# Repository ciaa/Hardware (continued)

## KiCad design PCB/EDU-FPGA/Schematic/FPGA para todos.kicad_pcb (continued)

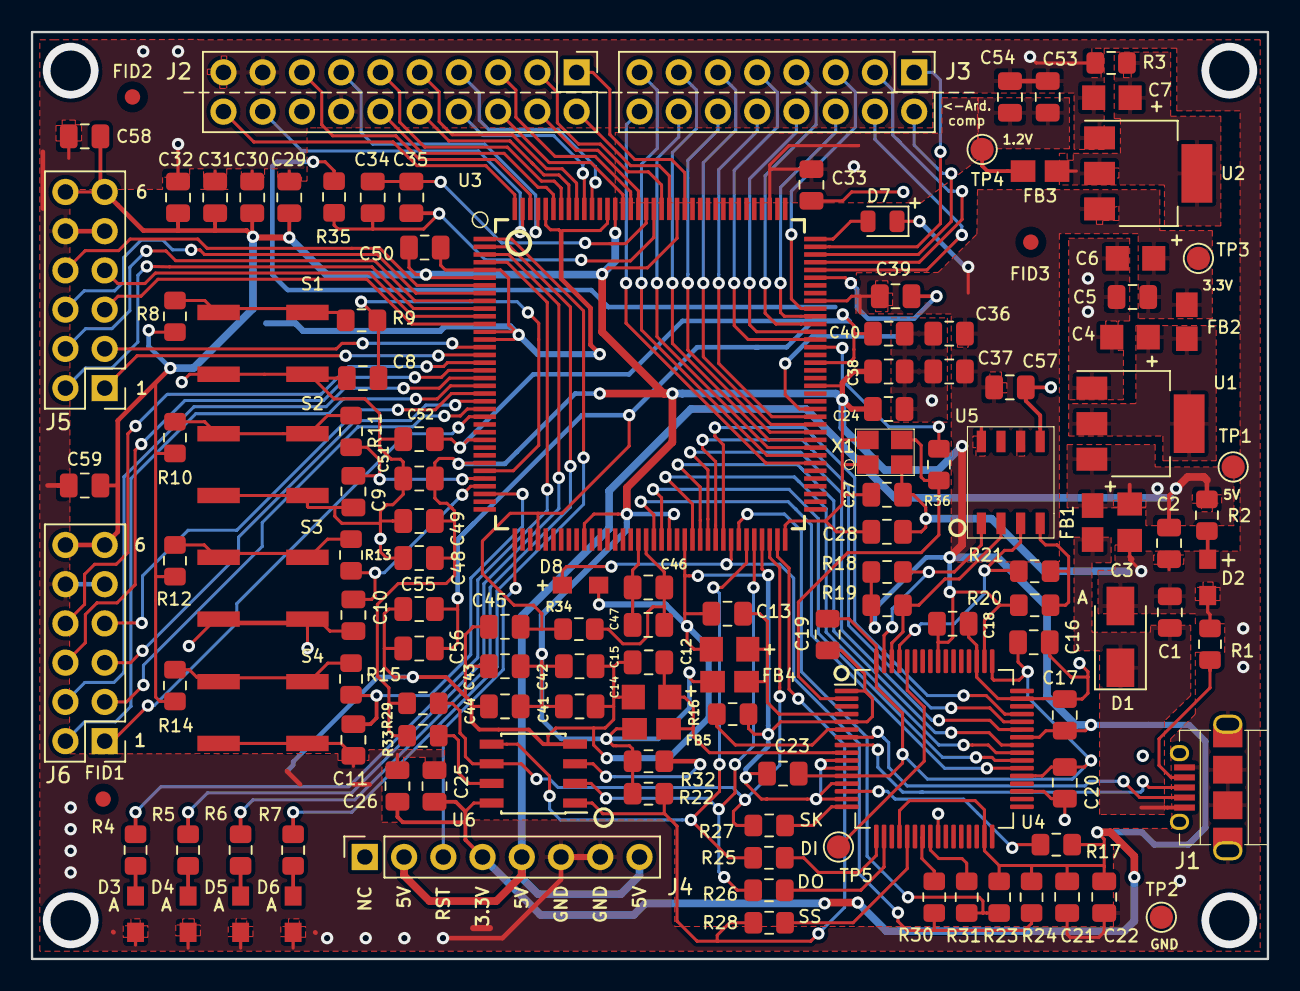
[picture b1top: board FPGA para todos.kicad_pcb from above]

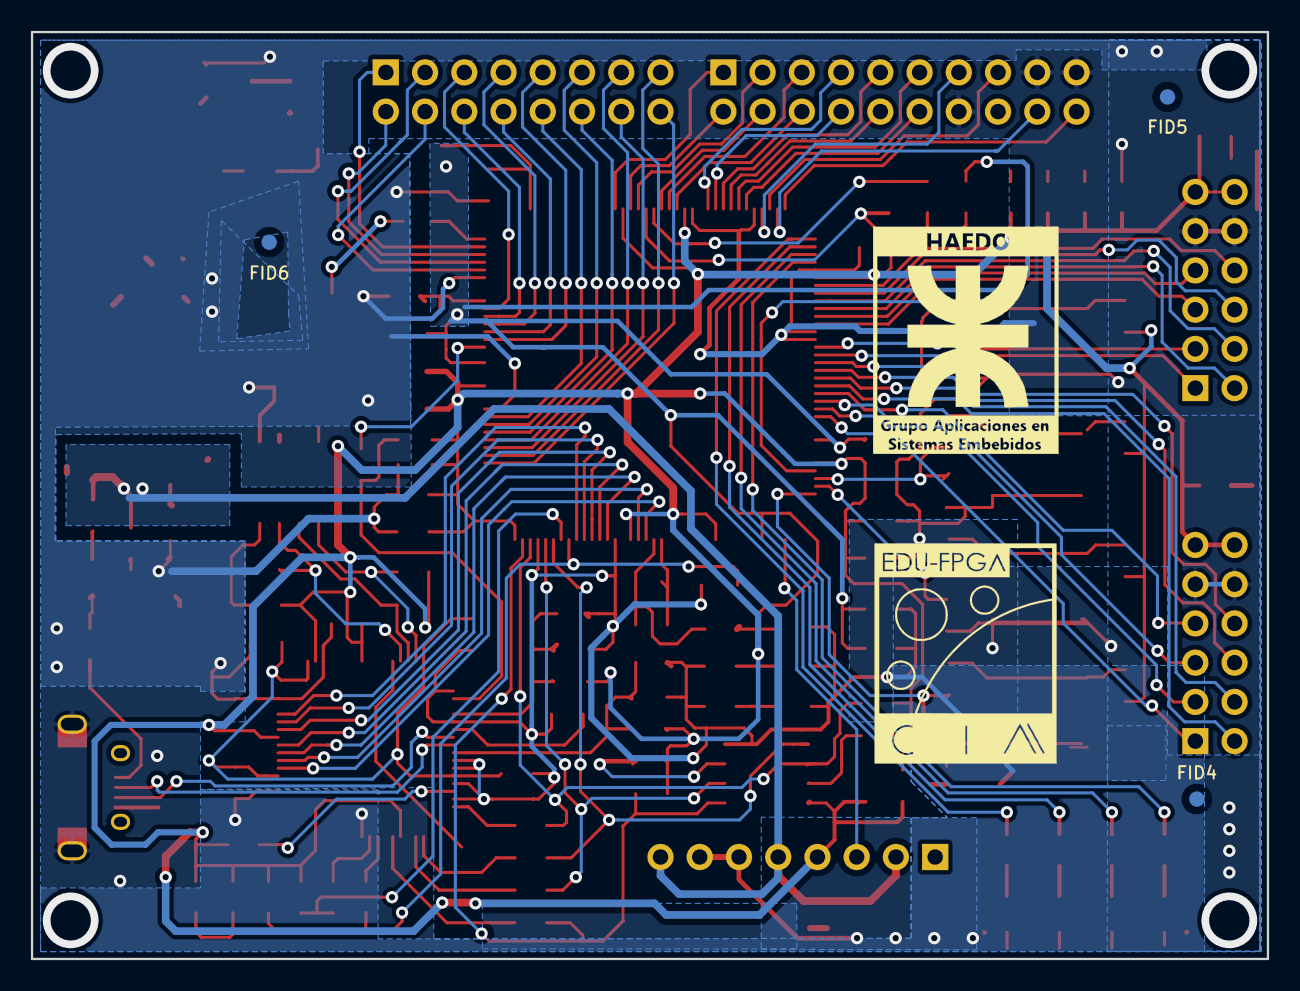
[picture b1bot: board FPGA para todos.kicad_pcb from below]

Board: 2 copper layers, 80.0 x 60.0 mm, 136 parts (3 on the bottom side), 114 nets.

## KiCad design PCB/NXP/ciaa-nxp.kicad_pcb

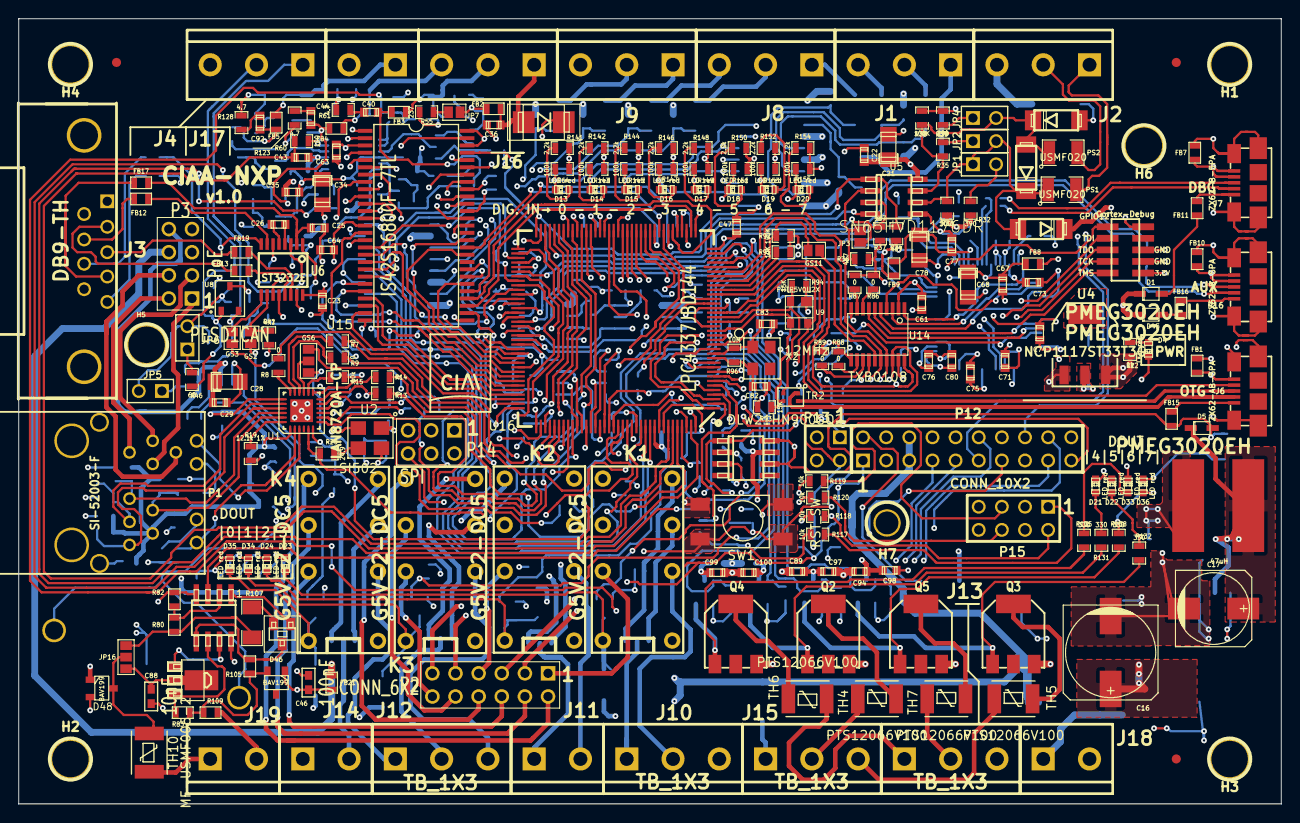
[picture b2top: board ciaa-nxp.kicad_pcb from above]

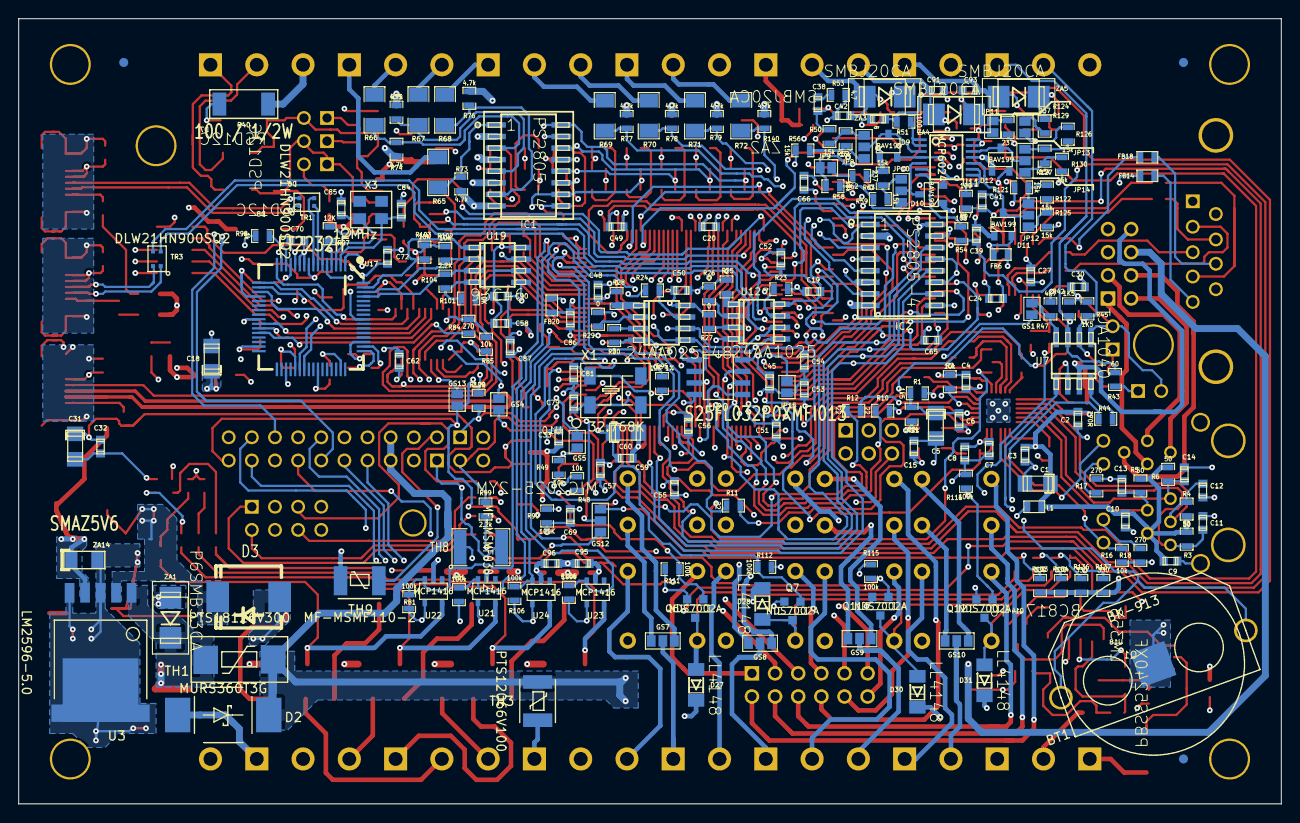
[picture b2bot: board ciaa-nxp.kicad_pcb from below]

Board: 4 copper layers, 138.6 x 86.2 mm, 443 parts (212 on the bottom side), 375 nets.

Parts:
BT1: BK-913; BK-913-ND
C1, C5, C18, C31, C34, C68, C78: 10uF; c_1206_tantalio_1
C2, C3, C4, C6, C9, C10, C15, C19, C20, C22, C23, C24, C25, C26, C27, C29, C30, C32, C33, C35, C37, C39, C41, C43, C45, C47, C48, C49, C50, C51, C52, C53, C54, C55, C56, C57, C58, C59, C61, C62, C63, C64, C65, C66, C67, C70, C71, C72, C73, C74, C75, C76, C77, C86, C87, C89, C90, C94, C95, C96: 100nF; c_0603
C7, C38, C40, C44, C92: 470pF; c_0603
C8, C36, C42, C91, C93: 1nF; c_0603
C11, C12, C13, C14: 18pF; c_0603
C16: 470uF; c_elec_10x10.5
C17: 330uF; c_elec_8x10
C21, C28: 10uF / 6V3; c_1206_tantalio
C46: 100nF; SMC0603
C60: 10uF; c_1206_tantalio
C69: 10nF; c_0603
C79, C81: 15p; c_0603
C80: 3.3uF; c_0603
C82, C83: 20p; c_0603
C84, C85: 22p; c_0603
C88: 10nF; SMC0603
C97, C98, C99, C100: 1uF; c_0603
D1, D5, D45: PMEG3020EH; SOD323
D2: MURS360T3G; CASE-403-03
D3: B540C-13-F; Diode-SMC_Standard_RevA_26July2010
D4, D13, D14, D15, D16, D17, D18, D19, D20, D21, D22, D23, D24, D33, D34, D35, D36: LED red; LED-0603
D6, D7, D8: PSD12C; DO214AA-1-2
D9, D10, D11, D12, D46, D48: BAV199; SOT23-DIODE
D27, D28, D30, D31: LL4148; MiniMelf
F1, F2, F3: fiducial; Fiducial_1mm_TOP
F4, F5, F6: fiducial; Fiducial_1mm_BOT
FB1, FB2, FB3, FB4, FB5, FB6, FB8, FB9, FB10, FB20, FB21: MMZ1608B601C; SM0603
FB7, FB11, FB14, FB15, FB16: BLM18KG221SN1; SM0603
FB12, FB13, FB17, FB18, FB19: BLM18BD470SN1; SM0603
GS1, GS2, GS3, GS4, GS5, GS11, GS13: GS2
GS6, GS7, GS8, GS9, GS10, GS12: GS3
H1, H2, H3, H4, H5, H6, H7: 4mm; 1pin
IC1, IC2: PS2805-4; -SOP16
J1, J2, J4, J8, J9, J10, J12, J13, J15, J16: TB_1X3; bornier3
J3: DB9-TH; K22X-E9P-NJ
J6: ZX62-AB-5PA; USB_microAB_ZX62-AB&B-5PA-11
J7: ZX62-B-5PA; USB_microAB_ZX62-AB&B-5PA-11
J11, J14, J17, J18, J19: TB_1X2; bornier2
JP1, JP2, JP4, JP5, JP6: JUMPER-2; PIN_ARRAY_2X1
JP3: JUMPER-2; GS2
JP7, JP9, JP11, JP13: JUMPER; GS2
JP8, JP10, JP12, JP14, JP16: JUMPER3; GS3
JP15: ISP; GS2
K1, K2, K3, K4: G5V-2-DC5; G5V-2
L1: BK1608HS220-T; SM0603
L2: 47uH; SRN1060
P1: SI-52003-F; RJ45_SI-52003-F_PoE_ETH
P2: CONN_6X2; PIN_ARRAY_6X2
P3: PoE; PIN_ARRAY_4X2
P8: Cortex-Debug; Pin_Array_5x2_1.27mm_SMD
P12: CONN_10X2; pin_array_10x2
P13: I2C; PIN_ARRAY_2X2
P14: SPI; PIN_ARRAY_3X2
P15: Analog; pin_array_4x2
P16: ZX62-B-5PA; USB_microAB_ZX62-AB&B-5PA-11
PS1, PS2: USMF020; SM1210
Q1: PBSS5240XF; -SOT89-321
Q2, Q3, Q4, Q5: FQT13N06L; SOT223_Opendous
Q6, Q7, Q11, Q12: NDS7002A; SOT23GDS
Q14: BC817-40; -SOT23
R1: 1k5; SM0603_Resistor
R2, R15, R16, R48, R49, R85, R117, R118, R119, R120: 10k; SM0603_Resistor
R3, R4, R5, R6: 50; SM0603_Resistor
R7, R8, R9, R13, R14, R23, R24, R25, R26, R27, R28, R29, R30, R86, R87, R88, R89: 0; SM0603_Resistor
R10, R11, R12: 22; SM0603_Resistor
R17, R18, R84: 270; SM0603_Resistor
R19: 12.1k 1%; SM0603_Resistor
R20: 24.9; SM0603_Resistor
R21, R31, R64, R81, R106, R108, R111, R112, R115, R116, R143, R145, R147, R149, R151, R153, R155: 100k; SM0603_Resistor
R22, R98: 1k; SM0603_Resistor
R32, R39: 390; SM0603_Resistor
R33, R38, R90, R92: 100K; SM0603_Resistor
R34, R36, R37, R41, R47: 4K7; SM0603_Resistor
R35: 220; SM0603_Resistor
R40: 100 / 1/2W; SMR2010
R42, R45: 1K5; SM0603_Resistor
R43, R46: 60; SM0603_Resistor
R44: 270R; SM0603_Resistor
R50, R52, R56, R58, R59, R63, R121, R122, R125, R126, R127, R130: 15k; SM0603_Resistor
R51, R54, R57, R60: 100; SM0603_Resistor
R53, R61, R123, R128: 4.7; SM0603_Resistor
R55, R62, R124, R129: 237; SM0603_Resistor
R65, R66, R67, R68, R69, R70, R71, R72: 3.3k; SM1206
R73, R74, R75, R76, R77, R78, R79, R140: 4.7k; SM0603_Resistor
R80: 33k; SM0603
R82: 15k; SM0603
R83: 24.9; SM0603
R91, R101, R102, R103: 10K; SM0603_Resistor
R93, R94: 15K; SM0603_Resistor
R95: 12K 1%; SM0603_Resistor
R96: 10M; SM0603_Resistor
R97: 12K; SM0603_Resistor
R99, R100, R141, R142, R144, R146, R148, R150, R152, R154: 2.2k; SM0603_Resistor
R104: 2.2K; SM0603_Resistor
R105: 2.49k; SM0603
R107: 2.2k; SM1206
R109: 10K; SM0603
R131, R132, R133, R134, R135, R136, R137, R138: 330; SM0603_Resistor
SW1: RST_SW; PUSH_SWITCH
TH1: PTS18126V300; MF-SM030
TH3, TH4, TH5, TH6, TH7: PTS12066V100; MF-MSMF
TH8: MF-MSMF030-2; SM1812
TH9: MF-MSMF110-2; MF-MSMF
TH10: MF-USMF005-2; MF-MSMF
TR1, TR2, TR3: DLW21HN900SQ2; SRF2012
U1: LAN8720A-CP; QFN24
U2: SI502; 4SMD
U3: LM2596-5.0; D2PACK5-LM2596
U4: NCP1117ST33T3G; SOT223
U5: SN65HVD1176DR; -SOIC8
U6: ST3232E; TSSOP16
U7: TJA1040; -SOIC8
U8: PESD1CAN; SOT23-3
U9: PRTR5V0U2X; sot143B
U10: MIC2025-2YM; -SOIC8
U11: MCP6024; TSSOP14
U12: 24AA1025; -SOIC8
U13: 24AA025E48; -SOIC8
U14: TXB0108; tssop-20
U15: IS42S16800F-7TL; TSOP54-M08-T2
U16: LPC4337JBD144; LQFP144-M05
U17: FT2232H; LQFP64-M05
U18: LM358; -SOIC8
U19: 93C46; -SOIC8
U20: S25FL032P0XMFI013; SO8
U21, U22, U23, U24: MCP1416; SOT23-5
X1: 32.768K; 4SOJ
X2, X3: 12MHz; FA238V-XTAL
ZA1: P6SMB33CA; -SMB
ZA2, ZA3, ZA4, ZA5: SMBJ20CA; -SMB
ZA14: SMAZ5V6; SOD123F

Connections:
+3.3V: C4.1, C5.1, C6.1, C15.1, C18.1, C19.1, C20.1, C23.1, C45.1, C47.2, C48.2, C49.2, C50.2, C51.2, C52.2, C53.2, C54.2, C55.2, C56.2, C57.2, C58.2, C61.2, C62.2, C63.1, C64.1, C65.1, C66.1, C73.1, C74.1, C75.1, C76.1, C90.1, FB6.1, FB8.2, FB9.2, L1.1, P8.1, R1.1, R2.1, R15.1, R16.1, R18.2, R21.2, R27.1, R28.1, R34.1, R49.1, R64.2, R90.2, R91.2, R92.2, R98.1, R99.1, R100.1, R101.1, R102.1, R103.1, R141.2, R142.2, R143.2, R144.2, R145.2, R146.2, R147.2, R148.2, R149.2, R150.2, R151.2, R152.2, R153.2, R154.2, R155.2, TH8.1, U1.9, U2.4, U4.2, U6.16, U12.8, U13.8, U14.2, U14.19, U15.1, U15.3, U15.9, U15.14, U15.27, U15.43, U15.49, U16.5, U16.25, U16.36, U16.41, U16.59, U16.71, U16.77, U16.94, U16.107, U16.111, U16.131, U16.141, U17.20, U17.31, U17.42, U17.50, U17.56, U19.6, U19.8, U20.8
+3.3VADC: C34.1, C35.1, C59.1, C60.2, C86.1, C87.1, D9.1, D10.1, D11.1, D12.1, FB6.2, U11.4, U16.16, U16.17, U16.137
+5V: C17.1, C21.2, C22.1, C28.2, C29.2, C33.1, C89.2, C94.2, C95.2, C96.2, C97.2, C98.2, C99.2, C100.2, D1.2, D5.2, D8.1, D27.2, D28.2, D30.2, D31.2, D45.2, K1.1, K2.1, K3.1, K4.1, L2.2, P3.8, R22.1, R32.1, R33.1, R133.2, R134.2, R136.2, R137.2, TH9.2, U3.4, U4.3, U5.8, U7.3, U10.7, U21.2, U22.2, U23.2, U24.2, ZA14.2
+24V: D2.2, FB21.1, P3.6, P12.5, P12.6, TH1.1, TH3.2
/CPU/AIN0: C37.1, R51.2, U16.2
/CPU/AIN1: C39.1, R54.2, U16.143
/CPU/AIN2: C41.1, R57.2, U16.139
/CPU/AIN3: C43.1, R60.2, U16.138
/CPU/AUX_CLK: P12.16, U16.99
/CPU/CAN_RD: R44.1, U16.114
/CPU/CAN_TD: U7.1, U16.116
/CPU/DIN0: D13.2, IC1.16, R64.1, U16.1
/CPU/DIN1: D14.2, IC1.14, R143.1, U16.3
/CPU/DIN2: D15.2, IC1.12, R145.1, U16.8
/CPU/DIN3: D16.2, IC1.10, R147.1, U16.7
/CPU/DIN4: D17.2, IC2.16, R149.1, U16.117
/CPU/DIN5: D18.2, IC2.14, R151.1, U16.132
/CPU/DIN6: D19.2, IC2.12, R153.1, U16.133
/CPU/DIN7: D20.2, IC2.10, R155.1, U16.134
/CPU/DOUT0: Q6.G, R111.1, U16.9
/CPU/DOUT1: Q7.G, R112.1, U16.10
/CPU/DOUT2: Q11.G, R115.1, U16.11
/CPU/DOUT3: Q12.G, R116.1, U16.81
/CPU/DOUT4: R106.1, U16.15, U24.3
/CPU/DOUT5: R81.1, U16.33, U22.3
/CPU/DOUT6: R108.1, U16.35, U23.3
/CPU/DOUT7: R31.1, U16.48, U21.3
/CPU/EECLK: R102.2, U17.62, U19.2
/CPU/EECS: R103.2, U17.63, U19.1
/CPU/EEDATA: R104.1, U17.61, U19.3
/CPU/EMA_A1: U15.24, U16.104
/CPU/EMA_A2: U15.25, U16.105
/CPU/EMA_A6: U15.31, U16.42
/CPU/EMC_A0: U15.23, U16.102
/CPU/EMC_A3: U15.26, U16.106
/CPU/EMC_A4: U15.29, U16.108
/CPU/EMC_A5: U15.30, U16.38
/CPU/EMC_A7: U15.32, U16.43
/CPU/EMC_A8: U15.33, U16.98
/CPU/EMC_A9: JP15.2, U15.34, U16.96
/CPU/EMC_A10: U15.22, U16.95
/CPU/EMC_A11: U15.35, U16.84
/CPU/EMC_A13: U15.20, U16.75
/CPU/EMC_A14: U15.21, U16.86
/CPU/EMC_CAS: U15.17, U16.80
/CPU/EMC_CKE: U15.37, U16.101
/CPU/EMC_CLK0: U15.38, U16.45
/CPU/EMC_D0: U15.2, U16.50
/CPU/EMC_D1: U15.4, U16.51
/CPU/EMC_D2: U15.5, U16.52
/CPU/EMC_D3: U15.7, U16.53
/CPU/EMC_D4: U15.8, U16.55
/CPU/EMC_D5: U15.10, U16.56
/CPU/EMC_D6: U15.11, U16.60
/CPU/EMC_D7: U15.13, U16.61
/CPU/EMC_D8: U15.42, U16.57
/CPU/EMC_D9: U15.44, U16.58
/CPU/EMC_D10: U15.45, U16.63
/CPU/EMC_D11: U15.47, U16.65
/CPU/EMC_D12: U15.48, U16.37
/CPU/EMC_D13: U15.50, U16.39
/CPU/EMC_D14: U15.51, U16.46
/CPU/EMC_D15: U15.53, U16.54
/CPU/EMC_DYCS: U15.19, U16.97
/CPU/EMC_LDQM: U15.15, U16.103
/CPU/EMC_RAS: U15.18, U16.82
/CPU/EMC_UDQM: U15.39, U16.100
/CPU/EMC_WE: U15.16, U16.49
/CPU/ENET_CRS_DV: R12.1, U16.64
/CPU/ENET_MDC: R14.1, U16.140
/CPU/ENET_MDIO: R13.1, U16.66
/CPU/ENET_REF_CLK: R20.2, U1.5, U16.68
/CPU/ENET_RXD0: R10.1, U16.62
/CPU/ENET_RXD1: R11.1, U16.32
/CPU/ENET_TXD0: R7.1, U16.67
/CPU/ENET_TXD1: R8.1, U16.70
/CPU/ENET_TX_EN: R9.1, U16.34
/CPU/FT_OE: R84.2, U17.28
/CPU/FT_RST: U14.7, U17.27
/CPU/FT_TCK: U14.1, U17.16
/CPU/FT_TDI: U14.3, U17.17
/CPU/FT_TDO: U14.4, U17.18
/CPU/FT_TMS: U14.5, U17.19
/CPU/FT_TRST: U14.6, U17.26
/CPU/FT_XTIN: C84.2, U17.2, X3.2
/CPU/FT_XTOUT: C85.2, U17.3, X3.1
/CPU/GPIO0: GS6.3, P12.7, U16.74
/CPU/GPIO1: GS1.1, P12.8, U16.91
/CPU/GPIO2: GS2.1, P12.9, U16.110
/CPU/GPIO3: GS3.1, P12.10, P14.5, U16.85
/CPU/GPIO_AIN0_DAC: GS12.2, U16.6
/CPU/I2C_SCL: P13.2, R99.2, U12.6, U13.6, U16.92
/CPU/I2C_SDA: P13.1, R100.2, U12.5, U13.5, U16.93
/CPU/RS232_RXD: U6.12, U16.88
/CPU/RS232_TXD: U6.11, U16.87
/CPU/RS485_DIR: JP3.1, R37.1, U5.3, U16.78
/CPU/RS485_RXD: R34.2, U5.1, U16.72
/CPU/RS485_TXD: U5.4, U16.69
/CPU/RST: GS13.1, U14.14
/CPU/RTCX1: C81.2, U16.125, X1.4
/CPU/RTCX2: C79.2, U16.126, X1.1
/CPU/SPIFI_CS: U16.124, U20.1
/CPU/SPIFI_IO2: U16.121, U20.3
/CPU/SPIFI_IO3: U16.119, U20.7
/CPU/SPIFI_MISO: U16.122, U20.2
/CPU/SPIFI_MOSI: U16.123, U20.5
/CPU/SPI_MISO: P14.1, U16.44
/CPU/SPI_MOSI: P14.2, U16.47
/CPU/SPI_SCK: P14.6, U16.120
/CPU/TCK: P8.4, U14.20, U16.27
/CPU/TDI: P8.8, U14.18, U16.26
/CPU/TDO: P8.6, U14.17, U16.31
/CPU/TMS: P8.2, U14.16, U16.30
/CPU/TRST: GS11.1, U14.15
/CPU/U2_RXD: U16.115, U17.38
/CPU/U2_TXD: U16.113, U17.39
/CPU/USB_AUX_DM: TR3.2, U16.90
/CPU/USB_AUX_DP: TR3.3, U16.89
/CPU/USB_DEBUG_VBUS: D1.1, FB11.2
/CPU/USB_DM: R94.1, TR2.2, U9.2, U16.20
/CPU/USB_DP: R93.1, TR2.3, U9.3, U16.18
/CPU/USB_ID: J6.4, U16.22
/CPU/USB_JTAG_1.8V: C70.1, C71.1, C72.1, C80.1, U17.12, U17.37, U17.49, U17.64
/CPU/USB_JTAG_DM: TR1.2, U17.7
/CPU/USB_JTAG_DP: TR1.3, U17.8
/CPU/USB_VBUS: C31.1, C32.1, D5.1, FB15.2, U9.4, U10.6, U10.8, U16.21
/CPU/XTAL1: C82.2, R96.2, U16.12, X2.2
/CPU/XTAL2: C83.2, R96.1, U16.13, X2.1
/CPU/nTRST: GS11.2, R92.1, U16.29
/Entradas Digitales/COM: IC1.2, IC1.4, IC1.6, IC1.8, IC2.2, IC2.4, IC2.6, IC2.8, J9.3, R73.1, R74.1, R75.1, R76.1, R77.1, R78.1, R79.1, R140.1
/Entradas Digitales/IN0: J1.1, R65.1
/Entradas Digitales/IN1: J1.2, R66.1
/Entradas Digitales/IN2: J1.3, R67.1
/Entradas Digitales/IN3: J8.1, R68.1
/Entradas Digitales/IN4: J8.2, R69.1
/Entradas Digitales/IN5: J8.3, R70.1
/Entradas Digitales/IN6: J9.1, R71.1
/Entradas Digitales/IN7: J9.2, R72.1
/Ethernet/LED_100M: P1.15, R16.2, U1.2
/Ethernet/LED_LINK: P1.12, U1.3
/Ethernet/PHY_nRESET: GS6.2, U1.15
/GPIO/AN0: GS12.3, R117.1
/GPIO/AN1: R119.1, U16.144
/GPIO/AN2: R118.1, U16.142
/GPIO/AN3: R120.1, U16.136
/GPIO/GPIO4: P12.11, U16.73
/GPIO/GPIO5: P12.12, U16.112
/GPIO/GPIO6: P12.13, U16.14
/GPIO/GPIO7: GS4.1, P12.14, U16.79
/GPIO/GPIO8: GS5.1, P12.15, U16.83
/GPIO/GPIO10: P12.17, U16.129
/GPIO/GPIO11: P12.18, U16.130
/GPIO/GPIO12: C69.1, GS6.1, GS13.2, P8.10, P12.19, R90.1, SW1.1, SW1.2, U16.128
/GPIO/USB_VBUS: D45.1, FB16.2
/GPIO/USR_3.3V: P12.1, P13.3, P14.3, TH8.2
/GPIO/USR_5V: P12.2, TH9.1
/Memorias NV/SPIFI_CLK: U16.118, U20.6
/RS485_RS232_CAN/CAN_H: J4.1, R42.2, R43.1, U7.7, U8.2
/RS485_RS232_CAN/CAN_L: J4.2, R45.1, R46.1, U7.6, U8.1
/RS485_RS232_CAN/CAN_STB: GS1.2, R47.2, U7.8
/RS485_RS232_CAN/RS232_CTS: GS3.2, U6.9
/RS485_RS232_CAN/RS232_RTS: GS2.2, R41.1, U6.10
/Salida Analógica/24V_A: C46.1, D46.3, D48.1, FB21.2, U18.8
/Salida Analógica/DAC_OUT: GS12.1, U18.3
/Salidas Digitales/C1A: J10.2, K1.4
/Salidas Digitales/C1B: K1.13, P2.1
/Salidas Digitales/C2A: J11.2, K2.4
/Salidas Digitales/C2B: K2.13, P2.7
/Salidas Digitales/C3A: J12.3, K3.4
/Salidas Digitales/C3B: K3.13, P2.12
/Salidas Digitales/C4A: J12.1, K4.4
/Salidas Digitales/C4B: K4.13, P2.6
/Salidas Digitales/NC1A: GS7.1, K1.6
/Salidas Digitales/NC1B: K1.11, P2.3
/Salidas Digitales/NC2A: GS8.1, K2.6
/Salidas Digitales/NC2B: K2.11, P2.9
/Salidas Digitales/NC3A: GS9.1, K3.6
/Salidas Digitales/NC3B: K3.11, P2.10
/Salidas Digitales/NC4A: GS10.1, K4.6
/Salidas Digitales/NC4B: K4.11, P2.4
/Salidas Digitales/NO1A: GS7.3, K1.8
/Salidas Digitales/NO1B: K1.9, P2.5
/Salidas Digitales/NO2A: GS8.3, K2.8
/Salidas Digitales/NO2B: K2.9, P2.11
/Salidas Digitales/NO3A: GS9.3, K3.8
/Salidas Digitales/NO3B: K3.9, P2.8
/Salidas Digitales/NO4A: GS10.3, K4.8
/Salidas Digitales/NO4B: K4.9, P2.2
/USB OTG/USB0_PPWR: GS4.2, R48.2, U10.1
/USB OTG/USB0_PWR_FAULT: GS5.2, R49.2, U10.2
GND: BT1.2, C1.2, C2.2, C3.2, C4.2, C5.2, C6.2, C7.2, C8.2, C9.2, C10.2, C11.2, C12.2, C13.2, C14.2, C15.2, C16.2, C17.2, C18.2, C19.2, C20.2, C21.1, C22.2, C23.2, C25.2, C27.2, C28.1, C29.1, C30.2, C31.2, C32.2, C33.2, C45.2, C47.1, C48.1, C49.1, C50.1, C51.1, C52.1, C53.1, C54.1, C55.1, C56.1, C57.1, C58.1, C61.1, C62.1, C63.2, C64.2, C65.2, C66.2, C67.2, C68.2, C69.2, C70.2, C71.2, C72.2, C73.2, C74.2, C75.2, C76.2, C77.2, C78.2, C79.1, C80.2, C81.1, C82.1, C83.1, C84.1, C85.1, C89.1, C90.2, C94.1, C95.1, C96.1, C97.1, C98.1, C99.1, C100.1, D3.1, D4.2, D7.2, D21.2, D22.2, D33.2, D36.2, FB1.1, FB7.2, FB10.1, FB14.2, FB20.1, IC1.9, IC1.11, IC1.13, IC1.15, IC2.9, IC2.11, IC2.13, IC2.15, J3.10, J3.11, J4.3, J6.5, J7.4, J7.5, J10.3, J14.1, J18.2, JP15.1, P1.6, P1.7, P1.16, P1.17, P3.5, P3.7, P8.3, P8.5, P8.9, P12.3, P12.4, P13.4, P14.4, P16.4, P16.5, Q2.3, Q3.3, Q4.3, Q5.3, Q6.S, Q7.S, Q11.S, Q12.S, R17.1, R19.2, R23.2, R24.2, R25.1, R26.1, R29.1, R30.1, R31.2, R36.2, R37.2, R38.2, R39.2, R40.1, R41.2, R47.1, R48.1, R81.2, R85.2, R86.1, R87.1, R88.1, R89.1, R93.2, R94.2, R95.2, R97.1, R106.2, R108.2, R111.2, R112.2, R115.2, R116.2, SW1.3, SW1.4, U1.GND, U2.2, U3.3, U3.5, U4.1, U5.5, U6.15, U7.2, U8.3, U9.1, U10.3, U12.4, U13.4, U14.11, U15.6, U15.12, U15.28, U15.41, U15.46, U15.52, U15.54, U16.4, U16.40, U16.76, U16.109, U17.1, U17.5, U17.10, U17.11, U17.13, U17.15, U17.25, U17.35, U17.47, U17.51, U19.5, U19.7, U20.4, U21.4, U22.4, U23.4, U24.4, ZA1.2, ZA14.1
GNDA: C34.2, C35.2, C36.2, C37.2, C39.2, C41.2, C42.2, C43.2, C46.2, C59.2, C60.1, C86.2, C87.2, C88.1, C91.2, C93.2, D9.3, D10.3, D11.3, D12.3, D48.3, FB20.2, J17.2, J19.2, P15.3, P15.4, P15.7, P15.8, R53.1, R55.1, R56.1, R61.1, R62.1, R63.1, R82.1, R109.1, R123.1, R124.1, R125.1, R128.1, R129.1, R130.1, U11.11, U16.19, U16.23, U16.135, U18.4, ZA2.1, ZA3.1, ZA4.1, ZA5.1
unnamed: R84.1, R85.1, U14.10
unnamed: R89.2, U14.13
unnamed: R86.2, U14.8
unnamed: R88.2, U14.12
unnamed: R87.2, U14.9
unnamed: R97.2, U17.6
unnamed: R98.2, U17.14
unnamed: R101.2, R104.2, U19.4
unnamed: FB7.1, J7.6, J7.7
unnamed: J7.3, TR1.4
unnamed: J7.2, TR1.1
unnamed: BT1.1, U16.127
unnamed: C67.1, C68.1, FB8.1, U17.9
unnamed: FB11.1, J7.1
unnamed: C77.1, C78.1, FB9.1, U17.4
unnamed: R91.1, U16.28
unnamed: R95.1, U16.24
unnamed: C24.1, U6.1
unnamed: C26.1, U6.4
unnamed: C24.2, U6.3
unnamed: J2.2, PS2.2
unnamed: JP3.2, R36.1, U5.2
unnamed: J2.3, R40.2
unnamed: J2.1, PS1.2
unnamed: C26.2, U6.5
unnamed: D6.2, D7.1, JP4.2, PS2.1, R35.2, R38.1, U5.7
unnamed: JP4.1, R39.1
unnamed: JP1.2, R32.2
unnamed: JP2.1, R35.1
unnamed: D6.1, D8.2, JP1.1, JP2.2, PS1.1, R33.2, U5.6
unnamed: JP5.1, R43.2
unnamed: JP6.1, R46.2
unnamed: FB13.1, U6.13
unnamed: FB12.1, U6.7
unnamed: FB18.1, U6.8
unnamed: FB18.2, J3.8
unnamed: FB19.1, U6.14
unnamed: FB17.2, J3.4
unnamed: C25.1, FB17.1, U6.2
unnamed: FB19.2, J3.3
unnamed: R44.2, U7.4
unnamed: FB14.1, J3.5
unnamed: FB13.2, J3.2
unnamed: FB12.2, J3.7
unnamed: C30.1, JP5.2, JP6.2, R42.1, R45.2, U7.5
unnamed: C27.1, U6.6
unnamed: R28.2, U13.1
unnamed: R29.2, U13.2
unnamed: R30.2, U13.3
unnamed: R24.1, U13.7
unnamed: R27.2, U12.3
unnamed: R25.2, U12.1
unnamed: R26.2, U12.2
unnamed: R23.1, U12.7
unnamed: C16.1, TH1.2, U3.1, ZA1.1
unnamed: D2.1, J18.1
unnamed: D3.2, L2.1, U3.2
unnamed: D4.1, R22.2
unnamed: R19.1, U1.24
unnamed: C12.1, P1.3, R4.2, U1.20
unnamed: P1.14, R18.1
unnamed: P1.13, R17.2
unnamed: R11.2, U1.7
unnamed: R12.2, U1.11
unnamed: R14.2, U1.13
unnamed: R1.2, R13.2, U1.12
unnamed: R10.2, U1.8
unnamed: R7.2, U1.17
unnamed: R8.2, U1.18
unnamed: R9.2, U1.16
unnamed: R2.2, U1.10
unnamed: C14.1, P1.5, R6.2, U1.22
unnamed: C11.1, P1.1, R3.2, U1.21
unnamed: P1.11, P3.4
unnamed: P1.8, P3.1
unnamed: C1.1, C2.1, C3.1, C9.1, C10.1, L1.2, P1.2, R3.1, R4.1, R5.1, R6.1, U1.1, U1.19
unnamed: C13.1, P1.4, R5.2, U1.23
unnamed: P1.10, P3.3
unnamed: P1.9, P3.2
unnamed: R20.1, U2.3
unnamed: R15.2, U1.14
unnamed: R21.1, U2.1
unnamed: C7.1, C8.1, U1.6
unnamed: FB1.2, J6.6, J6.7
unnamed: J6.2, TR2.1
unnamed: J6.3, TR2.4
unnamed: FB15.1, J6.1
unnamed: C40.2, R61.2
unnamed: JP9.1, R62.2
unnamed: JP10.3, R58.1, R59.2
unnamed: JP10.1, R59.1, R63.2
unnamed: JP8.3, R50.1, R52.2
unnamed: JP8.1, R52.1, R56.2
unnamed: C42.1, FB3.1, J16.2, ZA3.2
unnamed: C44.2, R123.2
unnamed: JP11.1, R124.2
unnamed: JP12.3, R121.1, R122.2
unnamed: C40.1, FB3.2, JP9.2, R58.2
unnamed: D10.2, JP10.2, U11.5
unnamed: R57.1, U11.8, U11.9
unnamed: R60.1, U11.13, U11.14
unnamed: C36.1, FB2.1, J16.1, ZA2.2
unnamed: R54.1, U11.6, U11.7
unnamed: JP7.1, R55.2
unnamed: D9.2, JP8.2, U11.3
unnamed: R51.1, U11.1, U11.2
unnamed: C38.1, FB2.2, JP7.2, R50.2
unnamed: C38.2, R53.2
unnamed: JP14.3, R126.1, R127.2
unnamed: JP14.1, R127.1, R130.2
unnamed: C91.1, FB4.1, J16.3, ZA4.2
unnamed: C93.1, FB5.1, J17.1, ZA5.2
unnamed: JP12.1, R122.1, R125.2
unnamed: D11.2, JP12.2, U11.10
unnamed: C92.1, FB5.2, JP13.2, R126.2
unnamed: C44.1, FB4.2, JP11.2, R121.2
unnamed: D12.2, JP14.2, U11.12
unnamed: JP13.1, R129.2
unnamed: C92.2, R128.2
unnamed: FB16.1, P16.1
unnamed: P16.3, TR3.4
unnamed: P16.2, TR3.1
unnamed: P15.5, R119.2
unnamed: P15.2, R118.2
unnamed: P15.6, R120.2
unnamed: P15.1, R117.2
unnamed: FB10.2, P16.6, P16.7
unnamed: IC2.3, R70.2, R78.2
unnamed: D17.1, R148.1
unnamed: D18.1, R150.1
unnamed: D16.1, R146.1
unnamed: IC2.1, R69.2, R77.2
unnamed: D20.1, R154.1
unnamed: IC2.7, R72.2, R140.2
unnamed: D19.1, R152.1
unnamed: IC2.5, R71.2, R79.2
unnamed: D13.1, R141.1
unnamed: IC1.1, R65.2, R73.2
unnamed: IC1.3, R66.2, R74.2
unnamed: D15.1, R144.1
unnamed: IC1.7, R68.2, R76.2
unnamed: IC1.5, R67.2, R75.2
unnamed: D14.1, R142.1
unnamed: Q3.4, TH5.1
unnamed: Q4.4, TH6.1
unnamed: Q2.4, TH4.1
unnamed: D22.1, R132.1
unnamed: Q3.1, R132.2, U22.5
unnamed: D21.1, R131.1
unnamed: Q2.1, R131.2, U24.5
unnamed: J15.2, TH4.2
unnamed: J15.1, TH3.1
unnamed: J13.2, TH7.2
unnamed: J13.1, TH6.2
unnamed: D30.1, D34.2, K3.16, Q11.D
unnamed: D34.1, R136.1
unnamed: GS9.2, J12.2
unnamed: GS8.2, J11.1
unnamed: GS7.2, J10.1
unnamed: GS10.2, J14.2
unnamed: D36.1, R138.1
unnamed: D23.1, R133.1
unnamed: Q5.1, R138.2, U21.5
unnamed: D23.2, D27.1, K1.16, Q6.D
unnamed: D33.1, R135.1
unnamed: Q4.1, R135.2, U23.5
unnamed: D31.1, D35.2, K4.16, Q12.D
unnamed: D35.1, R137.1
unnamed: D24.2, D28.1, K2.16, Q7.D
unnamed: D24.1, R134.1
unnamed: Q5.4, TH7.1
unnamed: J15.3, TH5.2
unnamed: Q14.3, R105.1, U18.5
unnamed: Q14.1, U18.1
unnamed: Q14.2, R107.2
unnamed: JP16.1, R80.1, R107.1
unnamed: Q1.3, U18.7
unnamed: Q1.1, R83.1, U18.6
unnamed: D46.1, R83.2, R105.2, R109.2
unnamed: R80.2, R82.2, U18.2
unnamed: J19.1, TH10.2
unnamed: D48.2, JP16.2, TH10.1
unnamed: C88.2, JP16.3, Q1.2

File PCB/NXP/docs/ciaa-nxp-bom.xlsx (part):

Componente | Cantidad por PCB | Referencia | Descripción | Código Digi-Key | Código Mouser | Cantidad para 100 PCBs | Costo unitario (USD FOB DigiKey) | Costo por PCB (USD FOB DigiKey)
BK-913 | 1 | BT1 | Soporte batería CR2032 | BK-913-ND | 534-3003 | 100 | 0.27 | 0.27 | BK-913-ND | 534-3003
15p | 2 | C79 C81 | Cap. Cerámico 0603 | 1276-1296-1-ND | 77-VJ0603A150JXACBC | 200 | 0.0121 | 0.0242 | 1276-1296-1-ND | 77-VJ0603A150JXACBC
18pF | 4 | C11 C12 C13 C14 | Cap. Cerámico 0603 | 399-1052-1-ND | 80-C0603C180J5G | 400 | 0.0154 | 0.0616 | 399-1052-1-ND | 80-C0603C180J5G
20p | 2 | C82 C83 | Cap. Cerámico 0603 | 1276-1187-1-ND | 81-GRM39C200J50 | 200 | 0.0138 | 0.0276 | 1276-1187-1-ND | 81-GRM39C200J50
22p | 2 | C84 C85 | Cap. Cerámico 0603 | 445-1273-1-ND | 80-C0603C220J5G | 200 | 0.0138 | 0.0276 | 445-1273-1-ND | 80-C0603C220J5G
470pF | 5 | C7 C38 C40 C44 C92 | Cap. Cerámico 0603 | 399-1075-1-ND | 80-C0603C471K5R | 500 | 0.01652 | 0.0826 | 399-1075-1-ND | 80-C0603C471K5R
1nF | 5 | C8 C36 C42 C91 C93 | Cap. Cerámico 0603 | 399-1082-1-ND | 80-C0603C102K5R | 500 | 0.0112 | 0.056 | 399-1082-1-ND | 80-C0603C102K5R
10nF | 2 | C69 C88 | Cap. Cerámico 0603 | 399-1091-1-ND | 80-C0603C103K5R | 200 | 0.009 | 0.018 | 399-1091-1-ND | 80-C0603C103K5R
100nF | 57 | C2 C3 C4 C6 C9 C10 C15 C19 C20 C22 C23 C24 C25 C26 C27 C29 C30 C32 C33 C35 C37 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 | Cap. Cerámico 0603 | 399-1096-1-ND | 80-C0603C104K5R | 5700 | 0.0054 | 0.3078 | 399-1096-1-ND | 80-C0603C104K5R
3.3uF | 1 | C80 | Cap. Tantáleo SMD | 399-5502-1-ND | 80-C0603C335M9P | 100 | 0.0147 | 0.0147 | 399-5502-1-ND | 80-C0603C335M9P
10uF | 10 | C1 C5 C18 C31 C34 C60 C68 C78 C21 C28 | Cap. Tantáleo SMD | 399-10116-1-ND | 80-T491A106K0067280 | 1000 | 0.092 | 0.92 | 399-10116-1-ND | 80-T491A106K0067280
330uF | 1 | C17 | Cap. Aluminio SMD | 493-9422-1-ND | 647-UCW1E331MNL1GS | 100 | 0.4061 | 0.4061 | 493-9422-1-ND | 647-UCW1E331MNL1GS
470uF/35V | 1 | C16 | Cap. Aluminio SMD | 493-3961-1-ND | 647-UCL1V471MNL1GS | 100 | 1.517 | 1.517 | 493-3961-1-ND | 647-UCL1V471MNL1GS
BAV199 | 6 | D9 D10 D11 D12 D46 D48 | Array de diodos SMD | BAV199LT1GOSCT-ND | 863-BAV199LT1G | 600 | 0.08646 | 0.51876 | BAV199LT1GOSCT-ND | 863-BAV199LT1G
PMEG3020EH | 3 | D1 D5 D45 | Diodo Schottky | 568-4129-1-ND | 771-PMEG3020EH-T/R | 300 | 0.20752 | 0.62256 | 568-4129-1-ND | 771-PMEG3020EH-T/R
MURS360T3G | 1 | D2 | Diodo 600V 3A | MURS360T3GOSCT-ND | 863-MURS360T3G | 100 | 0.467 | 0.467 | MURS360T3GOSCT-ND | 863-MURS360T3G
B540C-13-F | 1 | D3 | Diodo Schottky | B540C-FDICT-ND | 621-B540C-F | 100 | 0.7344 | 0.7344 | B540C-FDICT-ND | 621-B540C-F
LED red | 17 | D4 D13 D16 D18 D20 D21 D22 D23 D24 D33 D34 D35 D36 D38 D40 D42 D44 | LED Rojo 0603 | 1080-1400-1-ND | 78-VLMS1300-GS08 | 1700 | 0.075 | 1.275 | 1080-1400-1-ND | 78-VLMS1300-GS08
PSD12C | 3 | D6 D7 D8 | TVS | P6SMB12CAT3GOSCT-ND | 863-P6SMB12CAT3G | 300 | 0.23832 | 0.71496 | P6SMB12CAT3GOSCT-ND | 863-P6SMB12CAT3G
LL4148 | 12 | D14 D15 D17 D19 D27 D28 D30 D31 D37 D39 D41 D43 | Diodo SOD80 | LL4148FSCT-ND | 78-LL4148 | 1200 | 0.01483 | 0.17796 | LL4148FSCT-ND | 78-LL4148
BZX585-B6V8 | 4 | D25 D26 D29 D32 | Zener 6V8 | 568-8467-1-ND | 771-BZX585-B6V8115 | 400 | 0.1158 | 0.4632 | 568-8467-1-ND | 771-BZX585-B6V8115
MMZ1608B601C | 11 | FB8 FB9 FB1 FB2 FB3 FB4 FB5 FB6 FB10 FB20 FB21 | EMI Filter 0603 | 445-2166-1-ND | 810-MMZ1608B601C | 1100 | 0.02508 | 0.27588 | 445-2166-1-ND | 810-MMZ1608B601C
BLM18KG221SN1 | 5 | FB7 FB11 FB14 FB15 FB16 | EMI Filter 0603 | 490-5255-1-ND | 81-BLM18KG221SN1D | 500 | 0.03484 | 0.1742 | 490-5255-1-ND | 81-BLM18KG221SN1D
BLM18BD470SN1 | 5 | FB12 FB13 FB17 FB18 FB19 | EMI Filter 0603 | 490-5211-1-ND | 81-BLM18BD470SN1D | 500 | 0.03484 | 0.1742 | 490-5211-1-ND | 81-BLM18BD470SN1D
PS2801-4 | 2 | IC1 IC2 | Optoacoplador SMD. | PS2801-4ACT-ND | 782-TCMT4100 | 200 | 2.3562 | 4.7124 | PS2801-4ACT-ND | 782-TCMT4100
DB9 | 1 | J3 | Conector DB9 macho para PCB Thru-hole | S9575-ND | 806-K22X-E9P-NJ | 100 | 0.5445 | 0.5445 | S9575-ND | 806-K22X-E9P-NJ
ZX62-AB-5PA | 1 | J6 | Conector micro USB tipo AB | H11635TR-ND | 798-ZX62-AB-5PA11 | 100 | 0.7744 | 0.7744 | H11635TR-ND | 798-ZX62-AB-5PA11
ZX62-B-5PA | 2 | J7 P16 | Conector micro USB tipo B | H11634CT-ND | 798-ZX62-B-5PA11 | 200 | 0.726 | 1.452 | H11634CT-ND | 798-ZX62-B-5PA11
TB_1X3 | 10 | J1 J8 J9 J10 J12 J13 J15 J16 J2 J4 | Bornes fijos x3 | ED2610-ND | FIX | 1000 | 0.264 | 2.64 | ED2610-ND | FIX
TB_1X2 | 5 | J11 J14 J17 J18 J19 | Bornes fijos x2 | ED2609-ND | FIX | 500 | 0.231 | 1.155 | ED2609-ND | FIX
JUMPER | 15 | JP1 JP2 JP3 JP4 JP5 JP6 JP7 JP9 JP11 JP13 JP8 JP10 JP12 JP14 JP16 | Jumper | 3M9580-ND | 649-68786-102LF | 1500 | 0.042 | 0.63 | 3M9580-ND | 649-68786-102LF
PINES 1x40 | 2 |  | Tira de pines 1x40 2.54mm | S1212EC-40-ND | 855-M20-9994045 | 200 | 0.4704 | 0.9408 | S1212EC-40-ND | 855-M20-9994045
G5V-2-DC5 | 4 | K1 K2 K3 K4 | Relé DPDT | Z767-ND | 653-G5V-2-DC5 | 400 | 1.98024 | 7.92096 | Z767-ND | 653-G5V-2-DC5
47uH | 1 | L2 | Inductor 3A SMD | SRN1060-470MCT-ND | 652-SRN1060-470M | 100 | 0.45 | 0.45 | SRN1060-470MCT-ND | 652-SRN1060-470M
BK1608HS220-T | 1 | L1 | Ferrite | MH1608-221YCT-ND | 963-BK1608HS220-T | 100 | 0.0348 | 0.0348 | MH1608-221YCT-ND | 963-BK1608HS220-T
J0011D01BNL | 1 | P1 | Conector Ethernet con trafos y LEDs integrados | 553-1483-ND | 673-J0011D01BNL | 100 | 5.909 | 5.909 | 553-1483-ND | 673-J0011D01BNL
PINES 2x40 | 1 |  | Tira de pines 2x40 2.54mm | S2012EC-40-ND | 571-41037770 | 100 | 0.8337 | 0.8337 | S2012EC-40-ND | 571-41037770
Cortex-Debug | 1 | P8 | Conector 10 pines SMD 1.27mm | 952-1389-ND | 855-M50-3600542 | 100 | 0.88 | 0.88 | 952-1389-ND | 855-M50-3600542
USMF020 | 2 | PS1 PS2 | Polyswitch | MF-USMF020-2CT-ND | 652-MF-USMF020-2 | 200 | 0.2264 | 0.4528 | MF-USMF020-2CT-ND | 652-MF-USMF020-2
PBSS5240XF | 1 | Q1 | Transistor PNP 40V 2A | 568-10522-1-ND | 771-PBSS5240XF | 100 | 0.2177 | 0.2177 | 568-10522-1-ND | 771-PBSS5240XF
BC817-40 | 1 | Q14 | Transistor NPN 45V 0.5A | BC817-40LT3GOSCT-ND | 863-BC817-40LT3G | 100 | 0.0797 | 0.0797 | BC817-40LT3GOSCT-ND | 863-BC817-40LT3G
IRF820S | 4 | Q2 Q4 Q8 Q10 | MOSFET-N de potencia SMD | IRF820SPBF-ND | 844-IRF820SPBF | 400 | 1.006 | 4.024 | IRF820SPBF-ND | 844-IRF820SPBF
NDS7002A | 8 | Q3 Q5 Q6 Q7 Q9 Q11 Q12 Q13 | MOSFET-N SMD SOT-23 | NDS7002ACT-ND | 512-NDS7002A | 800 | 0.11542 | 0.92336 | NDS7002ACT-ND | 512-NDS7002A
0 | 17 | R7 R8 R9 R13 R14 R23 R24 R25 R26 R27 R28 R29 R30 R86 R87 R88 R89 | Resistor SMD 0603 | 311-0.0GRCT-ND | 71-CRCW0603-0-E3 | 1700 | 0.00204 | 0.03468 | 311-0.0GRCT-ND | 71-CRCW0603-0-E3
4.7 | 4 | R53 R61 R123 R128 | Resistor SMD 0603 | 311-4.7GRCT-ND | 71-CRCW0603-4.7 | 400 | 0.00348 | 0.01392 | 311-4.7GRCT-ND | 71-CRCW0603-4.7
22 | 3 | R10 R11 R12 | Resistor SMD 0603 | 311-22GRCT-ND | 71-CRCW060322R0FKEAH | 300 | 0.00348 | 0.01044 | 311-22GRCT-ND | 71-CRCW060322R0FKEAH
24.9 0.1% 25ppm/°C | 2 | R20 R83 | Resistor SMD 0603 | A109954CT-ND | 660-RN731JTTD24R9B25 | 200 | 0.2823 | 0.5646 | A109954CT-ND | 660-RN731JTTD24R9B25
50 | 4 | R3 R4 R5 R6 | Resistor SMD 0603 | 311-49.9HRCT-ND | 71-CRCW0603-50-E3 | 400 | 0.00456 | 0.01824 | 311-49.9HRCT-ND | 71-CRCW0603-50-E3
60 | 2 | R43 R46 | Resistor SMD 0603 | 311-59.0HRCT-ND | 71-CRCW0603-59-E3 | 200 | 0.006 | 0.012 | 311-59.0HRCT-ND | 71-CRCW0603-59-E3
100 | 12 | R51 R54 R57 R60 R65 R67 R69 R71 R73 R75 R77 R79 | Resistor SMD 0603 | 311-100GRCT-ND | 71-CRCW0603-100-E3 | 1200 | 0.00204 | 0.02448 | 311-100GRCT-ND | 71-CRCW0603-100-E3
220 | 1 | R35 | Resistor SMD 0603 | 311-220GRCT-ND | 71-CRCW0603-220-E3 | 100 | 0.0045 | 0.0045 | 311-220GRCT-ND | 71-CRCW0603-220-E3
237 0.1% 25ppm/°C | 4 | R55 R62 R124 R129 | Resistor SMD 0603 | P237DBCT-ND | 667-ERA-3AEB2370V | 400 | 0.11 | 0.44 | P237DBCT-ND | 667-ERA-3AEB2370V
270 | 4 | R17 R18 R84 R44 | Resistor SMD 0603 | 311-270GRCT-ND | 71-CRCW0603-270-E3 | 400 | 0.00348 | 0.01392 | 311-270GRCT-ND | 71-CRCW0603-270-E3
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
